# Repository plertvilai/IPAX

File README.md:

# In Situ Plankton Assemblage eXplorer

This Github repository contains all information necessary to build the In Situ Plankton Assemblage eXplorer (IPAX). Here is a brief introduction to how to utilize the repository. 

# Detailed Guide

A detail building guide is given in the Building Guide subfolder. Note that this guide is written in HTML format. To read it, simply download the entire folder and use a browser to open the file [index.html](https://github.com/plertvilai/IPAX/blob/master/Building%20Guide/index.html "index.html"). 

# Fabrication Files

There are two folders containing files that are necessary for IPAX fabrication.
1. **Mechanicals** contains STL files that can be directly sent to a 3D printer to printout the mechanical parts. A STEP file is also included for users that are interested to develop the system further. The STEP file [Assembly Rev02 Revised for BES v3.step](https://github.com/plertvilai/IPAX/blob/master/Mechanicals/Assembly%20Rev02%20Revised%20for%20BES%20v3.step "Assembly Rev02 Revised for BES v3.step") contains CAD files of all the parts, including waterproof housing from Bluerobotics that can be opened with a CAD software for further development.
2. **PCBs** contains all files for the printed circuit boards in the IPAX. Each subfolder is for each PCB, and the folder fabrication contains Gerber files that can be sent directly to PCB manufacturers. Each subfolder also contains KiCAD files that users can use to develop the PCBs for fit their needs. 

# Firmware
The folder Firmware contains all software for the IPAX. 
### Control Board
This subfolder contains Arduino (.ino) files that can be uploaded to the control board of the IPAX. 
1. full_control_alwaysON is the main routine for the control board that set the Raspberry Pi to always ON.
2. full_control_interval is the main routine for the control board that turns the Raspberry Pi ON only at the specified time.
3. rtc_set is a temporary code that can be uploaded to the control board to set the real-time clock.

### Raspberry Pi
This subfolder contains Python files for the Raspberry Pi on the IPAX. 
1. connectArduino.py is a routine that allows the Raspberry Pi to communicate with the Arduino on the control board.
2. ipaxClass.py is the library for the IPAX.
3. ipaxDeploy.py is the main routine for deploying the IPAX.
4. shutdowncheck.py is the control script that allows the Raspberry Pi to be properly shutdown with an external switch on the housing and the control board.

The configuration subfolder contains all the configuration files needed to configure that Raspberry Pi.

# Bill of Materials
The folder BOM contains a single MS Excel file (.xlsx) that contains the detailed bill of materials of the IPAX.

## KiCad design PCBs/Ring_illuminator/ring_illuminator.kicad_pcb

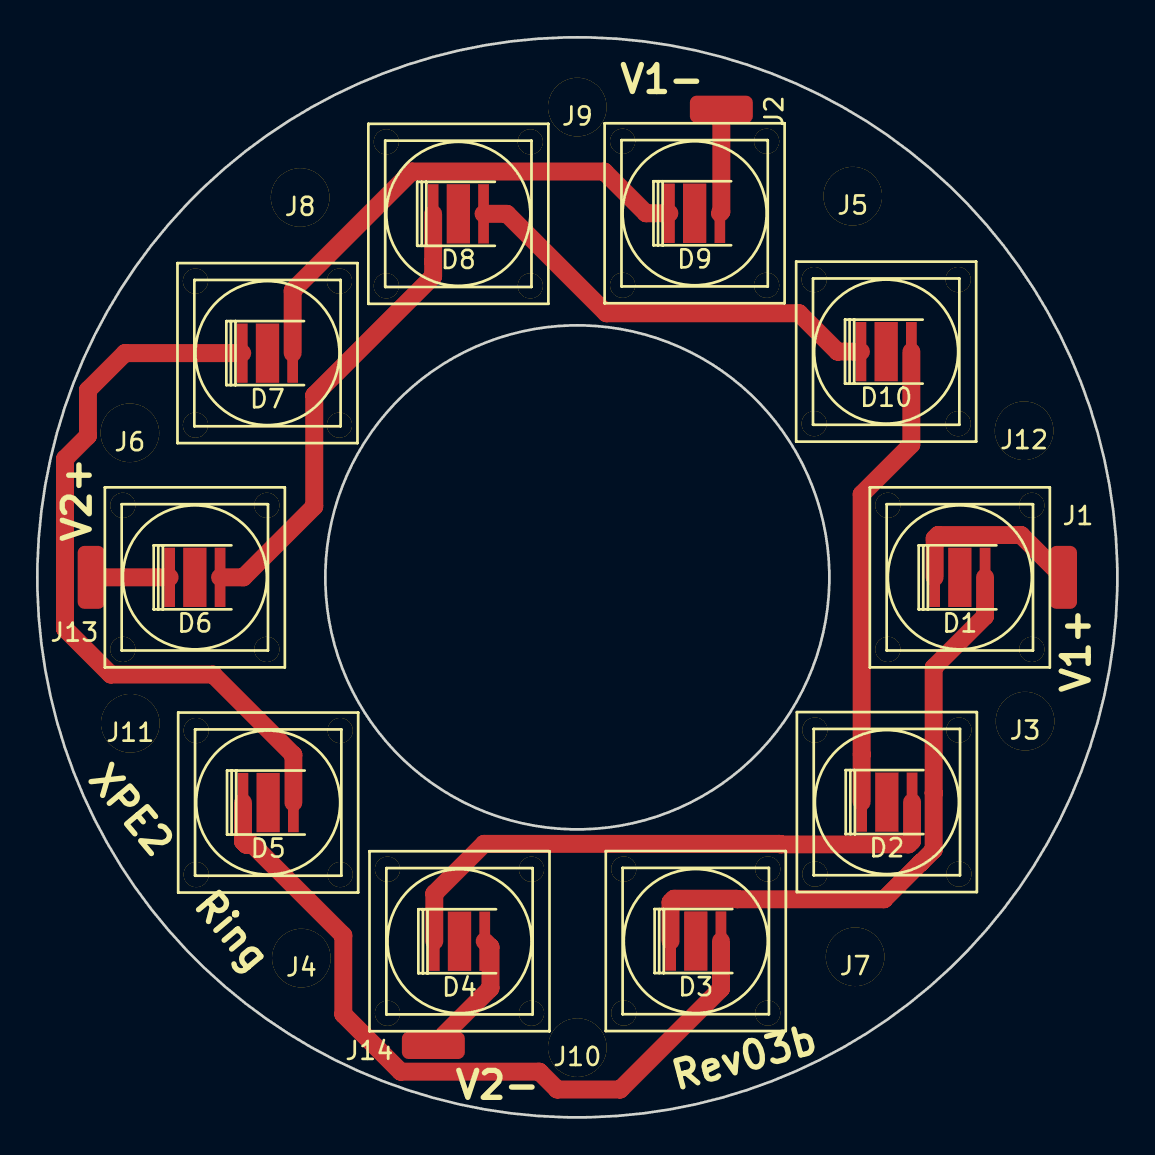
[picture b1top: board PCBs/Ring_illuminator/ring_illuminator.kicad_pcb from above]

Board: 2 copper layers, 60.0 x 60.0 mm, 24 parts (0 on the bottom side), 12 nets.

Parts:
D1, D2, D3, D4, D5, D6, D7, D8, D9, D10: LED; CREE_XTE_Carclo_10mm
J1, J2, J13, J14: Conn_01x01_Female; large_smd_pad
J3, J4, J5, J6, J7, J8, J9, J10, J11, J12: Conn_01x01_Female; SCREW_4

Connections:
LED1+: D1.2, J1.1
LED1-: D9.1, J2.1
LED2+: D6.2, J13.1
LED2-: D4.1, J14.1
unnamed: D1.1, D3.2
unnamed: D2.1, D4.2
unnamed: D3.1, D5.2
unnamed: D5.1, D7.2
unnamed: D6.1, D8.2
unnamed: D7.1, D9.2
unnamed: D2.2, D10.1
unnamed: D8.1, D10.2

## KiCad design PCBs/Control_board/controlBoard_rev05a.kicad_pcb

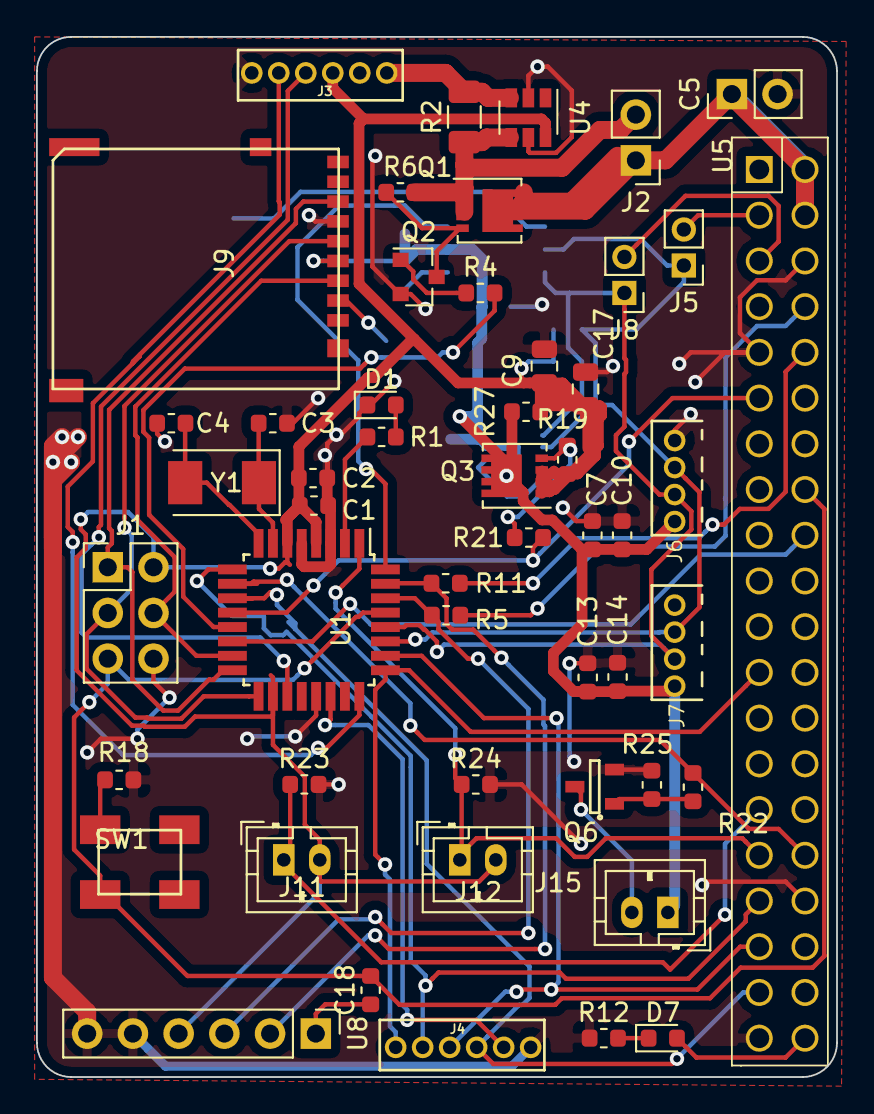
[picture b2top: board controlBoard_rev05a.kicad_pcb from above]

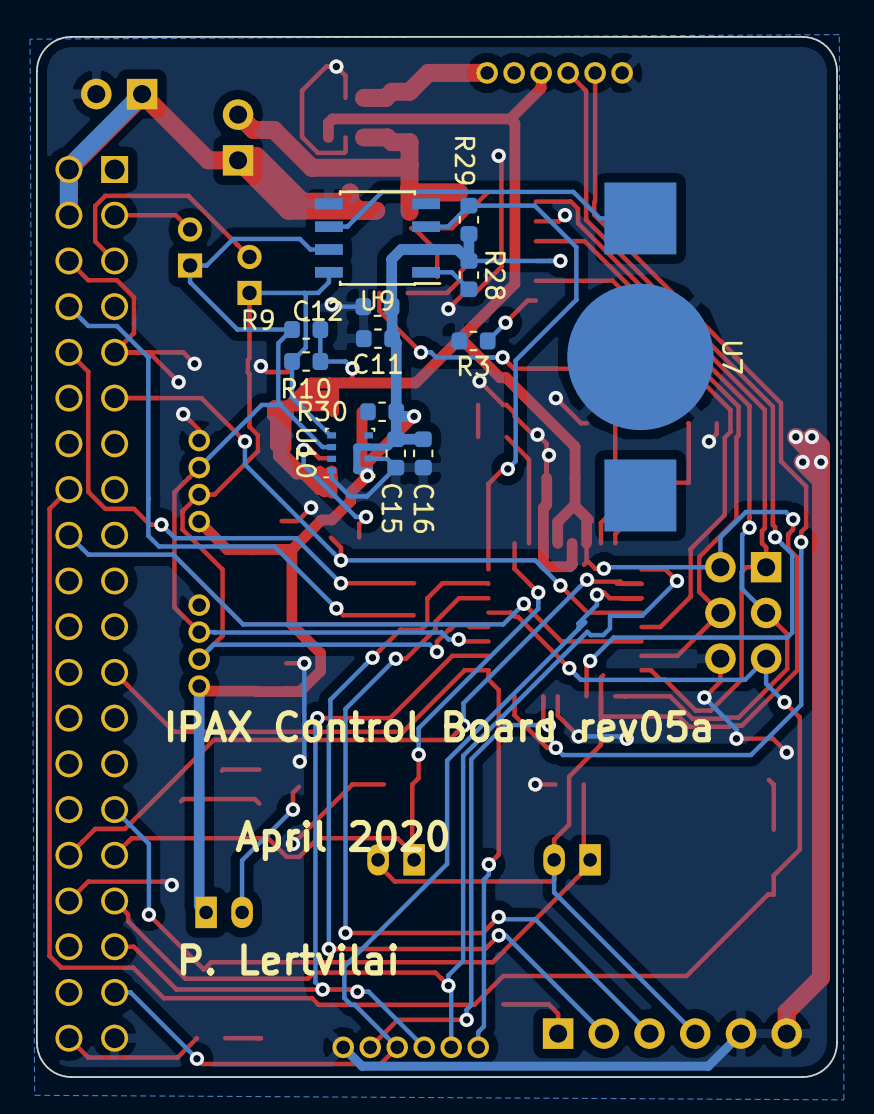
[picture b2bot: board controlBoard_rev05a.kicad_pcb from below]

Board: 2 copper layers, 44.5 x 57.8 mm, 64 parts (13 on the bottom side), 49 nets.

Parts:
C1, C10, C12, C14, C16: 1uF; C_0603_1608Metric
C2, C18: 0.1uF; C_0603_1608Metric
C3, C4: 22pF; C_0603_1608Metric
C5: CP; PinHeader_1x02_P2.54mm_Vertical
C7, C11, C13, C15: 10nF; C_0603_1608Metric
C9, C17: 22uF; C_0805_2012Metric
D1, D7: LED; LED_0603_1608Metric
J1: Conn_02x03_Odd_Even; PinHeader_2x03_P2.54mm_Vertical
J2: Conn_01x02_Male; PinHeader_1x02_P2.54mm_Vertical
J3, J4: Conn_01x06_Male; conn_1x06_1.5mm
J5, J8: Conn_01x02_Female; PinHeader_1x02_P2.00mm_Vertical
J6, J7: Conn_01x04_Male; conn_1x04_1.5mm
J9: Micro_SD_Card; DM3AT_microSD
J11, J12, J15: Conn_01x02_Male; JST_PH_B2B-PH-K_1x02_P2.00mm_Vertical
Q1, Q3: PMOS; Diodes_PowerDI3333-8
Q2: Q_NMOS_GSD; SOT-23
Q6: Q_NMOS_GSD; SOT-23-3
R1, R4, R5, R11, R12: 400R; R_0603_1608Metric
R2: 0.01R; R_1206_3216Metric
R3, R6, R9, R10, R18, R19, R23, R24, R25, R28, R29, R30: 10k; R_0603_1608Metric
R21, R22: 500R; R_0603_1608Metric
R27: jumper; R_0603_1608Metric
SW1: SW_DPST; SMD_pushbutton
U1: ATmega328P-AU; TQFP-32_7x7mm_P0.8mm
U4: INA181; SOT-23-6
U5: Pi_Header; RPi_Cobbler
U7: coin_cell; BK870_CR1025holder
U8: FTDI_Basic; PinHeader_1x06_P2.54mm_Vertical
U9: DS3231MZ; SOIC-8_3.9x4.9mm_P1.27mm
U10: BME280; Bosch_LGA-8_2.5x2.5mm_P0.65mm_ClockwisePinNumbering
Y1: Crystal; Crystal_SMD_Abracon_ABM3-2Pin_5.0x3.2mm

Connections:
3.3V_ARD: C1.1, C2.1, C9.1, C17.1, J1.2, J3.4, J11.2, J12.2, Q3.1, Q3.2, Q3.3, R9.1, R10.1, R19.2, R27.2, U1.4, U1.6, U1.18, U4.6, U8.4
3.3V_CTL: R21.1, U1.12, U5.6
3.3V_out: C7.1, C10.1, C11.1, C12.1, C13.1, C14.1, C15.1, C16.1, J6.1, J7.1, J9.4, J15.1, Q3.5, R27.1, R28.1, R29.1, R30.1, U9.2, U10.6, U10.8
5V: J2.2, Q1.1, Q1.2, Q1.3, R2.1, R6.2, U4.4
/Pi_SCL: J8.2, U5.3
/Pi_SDA: J5.2, U5.2
/powerControl/5V_IN: J3.6, R2.2, U4.3
CRYSTAL1: C3.1, U1.7, Y1.1
CRYSTAL2: C4.1, U1.8, Y1.2
CS: J9.2, R3.1
FAN_CTL: R22.2, U1.10, U5.25
Flash: J4.3, U1.11, U5.19
GND: C1.2, C2.2, C3.2, C4.2, C5.2, C7.2, C9.2, C10.2, C11.2, C12.2, C13.2, C14.2, C15.2, C16.2, C17.2, D1.1, J1.6, J3.1, J4.1, J6.4, J7.4, J9.6, Q2.2, Q6.2, R3.2, R12.1, R18.2, R23.2, R24.2, R25.1, U1.3, U1.5, U1.21, U4.2, U4.5, U5.5, U5.20, U5.24, U5.38, U7.1, U8.5, U8.6, U9.5, U10.1, U10.7
I_BATT: J3.3, U1.19
I_LED: J4.2, U1.22
LED_EN: J4.5, U1.9, U5.17
LED_EN2: J4.6, U1.25, U5.12
MISO: J1.1, J9.7, U1.16
MOSI: J1.4, J9.3, U1.15
unnamed: C18.1, U8.1
unnamed: D1.2, R1.1
unnamed: D7.1, R12.2
unnamed: D7.2, U5.21
unnamed: J15.2, Q6.3
unnamed: Q1.4, Q2.3, R6.1
unnamed: Q2.1, R4.1
unnamed: Q3.4, R19.1, R21.2
unnamed: Q6.1, R22.1, R25.2
unnamed: R1.2, U1.2
unnamed: R5.2, U5.37
unnamed: R11.2, U5.36
unnamed: R18.1, SW1.3
unnamed: R28.2, U9.1
unnamed: R30.2, U10.5
unnamed: U7.3, U9.6
PI_CTL: R4.2, U1.13
PI_SIG: U1.14, U5.32
PUSH: J11.1, R23.1, U5.15
PUSH2: J12.1, R24.1, U1.1, U5.16
RST: C18.2, J1.5, SW1.4, U1.29, U5.33
RXD: R5.1, U1.30, U8.3
SCK: J1.3, J9.5, U1.17
SCL: J6.2, J7.2, J8.1, R10.2, U1.28, U9.8, U10.4
SDA: J5.1, J6.3, J7.3, R9.2, U1.27, U9.7, U10.3
TXD: R11.1, U1.31, U8.2
Torch: J4.4, U1.26, U5.18
V_BATT: J3.2, U1.24
Vpi: C5.1, J2.1, Q1.5, U5.39, U5.40
alarm: R29.2, U1.32, U9.3

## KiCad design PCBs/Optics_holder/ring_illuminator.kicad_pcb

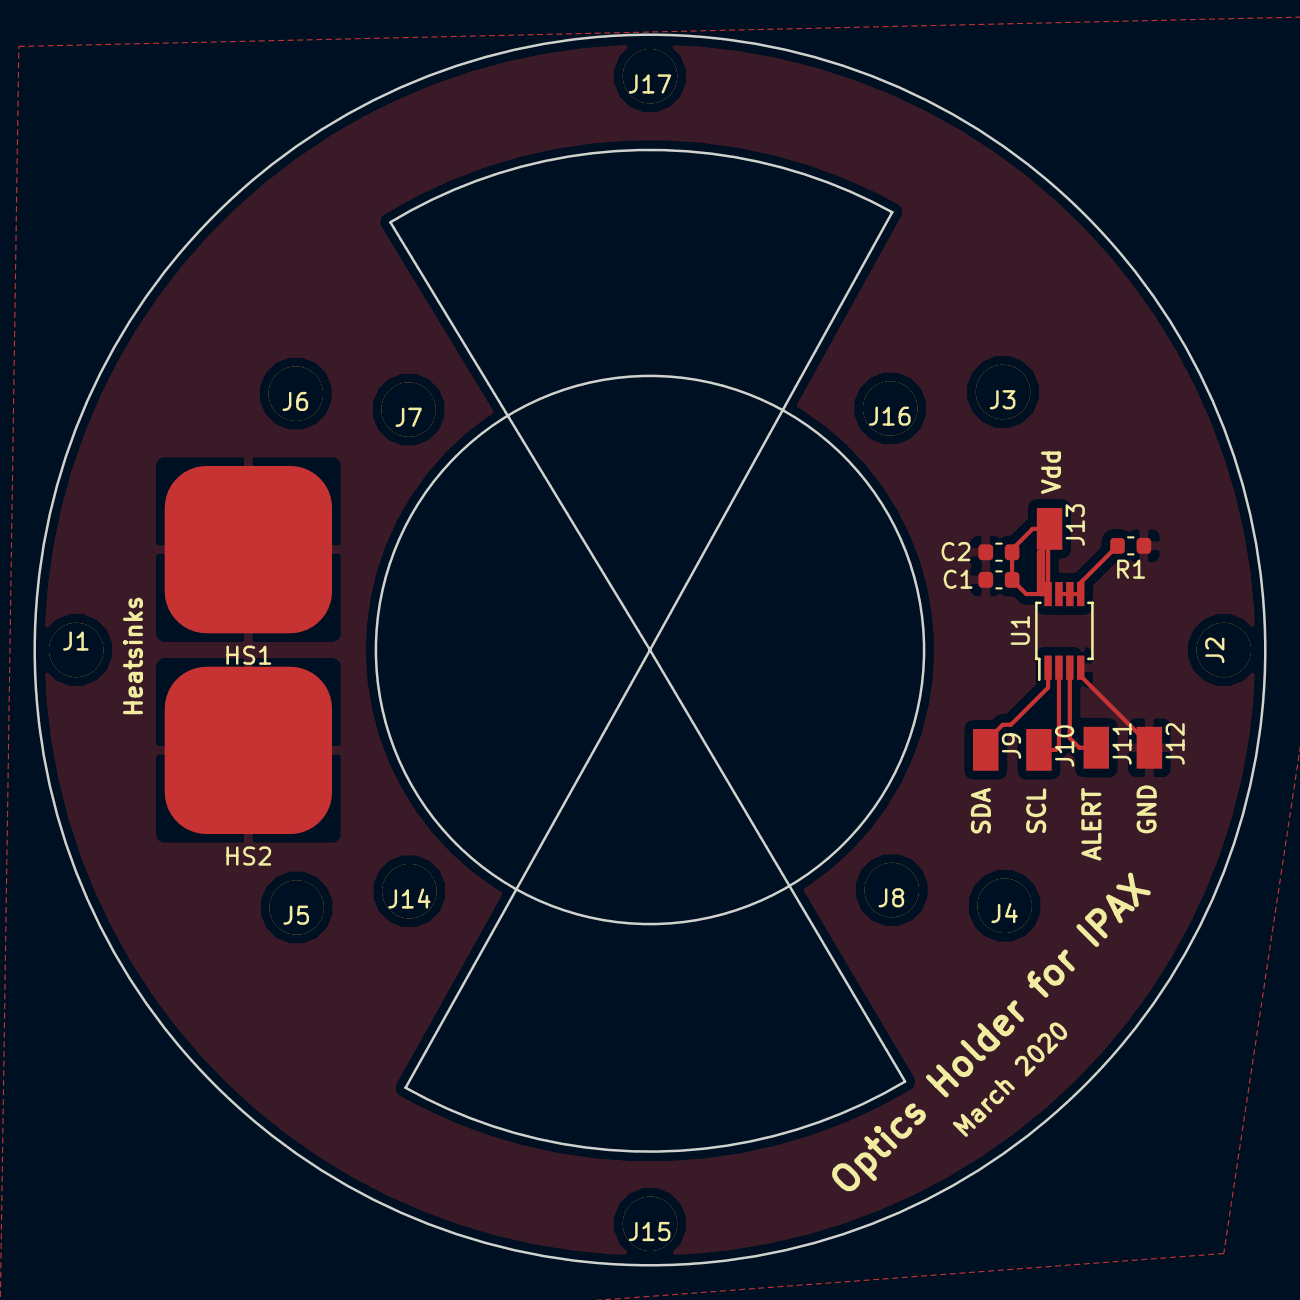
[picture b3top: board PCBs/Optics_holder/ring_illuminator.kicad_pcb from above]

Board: 2 copper layers, 73.5 x 73.5 mm, 23 parts (0 on the bottom side), 6 nets.

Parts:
C1, C2: C; C_0603_1608Metric
HS1, HS2: Heatsink_Pad; HeatSink_10x10mm
J1, J2, J3, J4, J5, J6, J7, J8, J14, J15, J16, J17: Conn_01x01_Female; SCREW_4
J9, J10, J11, J12, J13: Conn_01x01_Male; small_smd_pad
R1: 10k; R_0603_1608Metric
U1: MCP9808; MSOP-8_3x3mm_P0.65mm

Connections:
/A0: R1.2, U1.5, U1.6, U1.7
/ALERT: J11.1, U1.3
/SCL: J10.1, U1.2
/SDA: J9.1, U1.1
/Vdd: C1.1, C2.1, J13.1, U1.8
GND: C1.2, C2.2, HS1.1, HS2.1, J12.1, R1.1, U1.4

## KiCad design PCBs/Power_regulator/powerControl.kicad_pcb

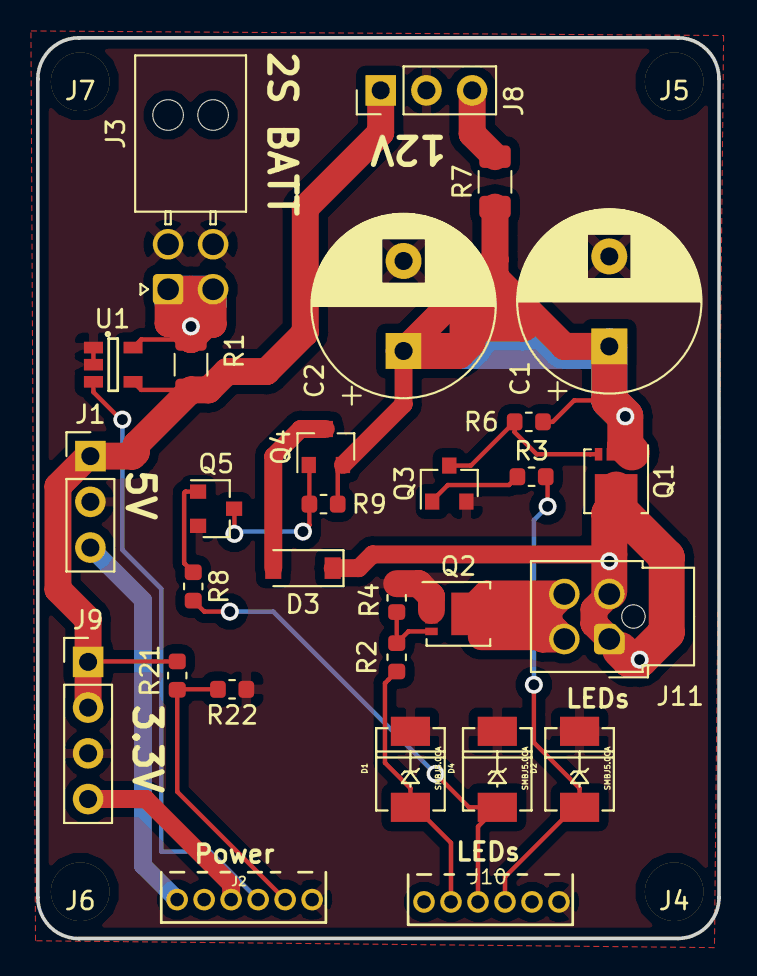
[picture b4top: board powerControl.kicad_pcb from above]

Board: 2 copper layers, 37.8 x 50.0 mm, 33 parts (0 on the bottom side), 20 nets.

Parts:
C1, C2: 470uF; CP_Radial_D10.0mm_P5.00mm
D1, D2, D4: SMBJ5.0CA; DO-214AA
D3: NSI450-20AT1G; D_SOD-123
J1, J8: Conn_01x03_Female; PinHeader_1x03_P2.54mm_Vertical
J2: Conn_01x06_Female; conn_1x06_1.5mm
J3: Conn_01x04_Male; Molex_Nano-Fit_105314-xx04_2x02_P2.50mm_Horizontal
J4, J5, J6, J7: Conn_01x01_Male; SCREW_4
J9: Conn_01x04_Female; PinHeader_1x04_P2.54mm_Vertical
J10: Conn_01x06_Male; conn_1x06_1.5mm
J11: Conn_01x04_Male; Molex_Nano-Fit_105310-xx04_2x02_P2.50mm_Vertical
Q1: PMOS; Diodes_PowerDI3333-8
Q2: NMOS; Diodes_PowerDI3333-8
Q3, Q5: Q_NMOS_GSD; SOT-23
Q4: Q_PMOS_GSD; SOT-23
R1: 0.01R; R_1206_3216Metric
R2, R3, R8: 400R; R_0603_1608Metric
R4, R6, R9, R21: 10k; R_0603_1608Metric
R7: 10R; R_1206_3216Metric
R22: 20k; R_0603_1608Metric
U1: MAX9938; SOT-23-5

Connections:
/3.3V: J2.4, J9.4
/5V: J1.3, J2.6
/12V: J8.3, R7.2
/I_batt: J2.3, U1.3
/Vbatt_in: J3.1, J3.2, R1.2, U1.5
/Vbatt_out: J1.1, J8.1, J9.1, J9.2, R1.1, R21.2, U1.4
/batt_sense: J2.2, R21.1, R22.2
Flash: D2.1, J10.3, R3.2
GND: C1.2, C2.2, D1.2, D2.2, D4.2, J1.2, J2.1, J3.3, J3.4, J8.2, J9.3, J10.1, Q2.1, Q2.2, Q2.3, Q3.2, Q5.2, R4.1, R22.1, U1.1, U1.2
LED+: D3.1, J11.1, J11.2, Q1.5
LED-: J11.3, J11.4, Q2.5
LED_EN: D1.1, J10.5, R2.2
unnamed: D3.2, Q4.3
unnamed: Q1.4, Q3.3, R6.1
unnamed: Q2.4, R2.1, R4.2
unnamed: Q3.1, R3.1
unnamed: Q4.1, Q5.3, R9.1
unnamed: Q5.1, R8.1
Torch: D4.1, J10.4, R8.2
V_LED: C1.1, C2.1, Q1.1, Q1.2, Q1.3, Q4.2, R6.2, R7.1, R9.2

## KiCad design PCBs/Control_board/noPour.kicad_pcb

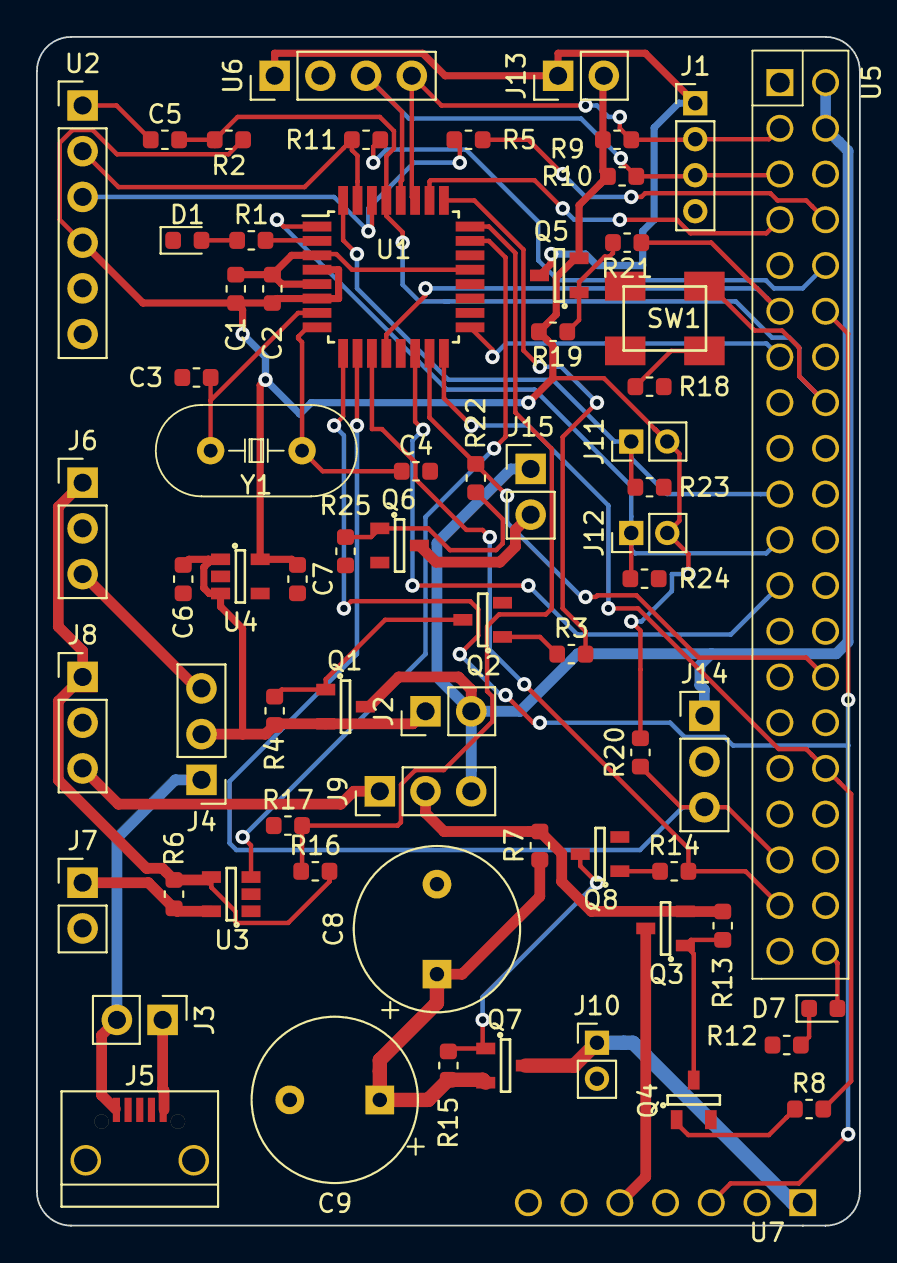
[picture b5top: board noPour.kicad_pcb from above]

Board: 2 copper layers, 45.7 x 66.0 mm, 68 parts (0 on the bottom side), 52 nets.

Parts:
C1, C6, C7: 1uF; C_0603_1608Metric
C2, C5: 0.1uF; C_0603_1608Metric
C3, C4: 22pF; C_0603_1608Metric
C8, C9: 1000uF; CP_Radial_Tantal_D9.0mm_P5.00mm
D1, D7: LED; LED_0603_1608Metric
J1: Conn_01x04_Male; PinHeader_1x04_P2.00mm_Vertical
J2, J3, J7, J13, J15: Conn_01x02_Male; PinHeader_1x02_P2.54mm_Vertical
J4, J6, J8, J9, J14: Conn_01x03_Male; PinHeader_1x03_P2.54mm_Vertical
J5: USB_B_Micro; USB_Micro-B_eBay
J10, J11, J12: Conn_01x02_Male; PinHeader_1x02_P2.00mm_Vertical
Q1, Q3, Q5, Q7: Q_PMOS_GSD; SOT-23-3
Q2, Q4, Q6, Q8: Q_NMOS_GSD; SOT-23-3
R1, R3, R5, R8, R11, R12, R14: 400R; R_0603_1608Metric
R2, R4, R9, R10, R13, R15, R18, R23, R24: 10k; R_0603_1608Metric
R6: 0.01R; R_0603_1608Metric
R7, R16, R17, R19, R20, R21, R22, R25: R; R_0603_1608Metric
SW1: SW_DPST; SMD_pushbutton
U1: ATmega328P-AU; TQFP-32_7x7mm_P0.8mm
U2: FTDI_Basic; PinHeader_1x06_P2.54mm_Vertical
U3: MAX9938; SOT-23-5
U4: AP2112; SOT-23-5
U5: Pi_Header; RPi_Cobbler
U6: OLED_I2C; PinHeader_1x04_P2.54mm_Vertical
U7: LUXdriver; LUXdrive
Y1: Crystal; CRYSTAL_TH

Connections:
3.3V: C1.1, C2.1, C7.1, J11.2, J12.2, J13.2, Q5.2, R2.1, R9.1, R10.1, R19.2, R20.2, U1.4, U1.6, U2.4, U4.5
3.3V_CTL: R21.1, U1.12, U5.6
3.3V_out: J1.1, J13.1, Q5.3, U6.1
12V: J8.3, J9.1
Batt_sense: R16.1, R17.2, U1.24
CRYSTAL1: C3.1, U1.7, Y1.1
CRYSTAL2: C4.1, U1.8, Y1.2
CUR_OUT: U1.23, U3.3
FAN_CTL: R22.2, U1.15, U5.27
Flash: R14.2, U1.11, U5.19
GND: C1.2, C2.2, C3.2, C4.2, C6.2, C7.2, C8.2, C9.2, D1.1, J1.4, J3.1, J5.5, J6.2, J7.2, J8.2, J10.2, J14.2, Q2.2, Q4.2, Q6.2, Q8.2, R12.1, R17.1, R18.2, R23.2, R24.2, R25.1, U1.3, U1.5, U1.21, U2.5, U2.6, U3.1, U3.2, U4.2, U5.5, U5.20, U5.24, U5.38, U6.2, U7.2, U7.7
GPIO4: U1.26, U5.4
GPIO10: U1.14, U5.12
GPIO27: U1.17, U5.7
LED+: J10.1, Q7.3, U7.1
LED_CTL: R8.2, U1.16, U5.25
LEDdim: U1.9, U5.35, U7.3
LUXin: Q3.3, U7.5
unnamed: C5.1, U2.1
unnamed: D1.2, R1.1
unnamed: D7.1, R12.2
unnamed: D7.2, U5.21
unnamed: J15.2, Q6.3
unnamed: Q1.1, Q2.3, R4.1
unnamed: Q2.1, R3.1
unnamed: Q3.1, Q4.3, R13.1
unnamed: Q4.1, R8.1
unnamed: Q5.1, R19.1, R21.2
unnamed: Q6.1, R22.1, R25.2
unnamed: Q7.1, Q8.3, R15.1
unnamed: Q8.1, R14.1
unnamed: R1.2, U1.2
unnamed: R5.2, U5.37
unnamed: R11.2, U5.36
unnamed: R18.1, SW1.3
PI_CTL: R3.2, U1.25
PUSH: J11.1, R23.1, U1.32, U5.10
PUSH2: J12.1, R24.1, U1.1, U5.11
RST: C5.2, R2.2, SW1.4, U1.29, U5.33
RXD: R5.1, U1.30, U2.3
SCL: J1.3, R10.2, U1.28, U5.3, U6.3
SDA: J1.2, R9.2, U1.27, U5.2, U6.4
TXD: R11.1, U1.31, U2.2
V_FLASH: C8.1, C9.1, Q7.2, R7.1, R15.2
V_LED: J9.2, Q3.2, R7.2, R13.2
Vbatt: J6.1, J8.1, R6.1, R16.2, U3.4
Vbatt0: J7.1, R6.2, U3.5
Vbatt_out: J4.3, J6.3
Vhall: J14.3, R20.1, U1.10, U5.18
Vin: C6.1, J2.1, J4.2, Q1.2, R4.2, U4.1, U4.3
Vpi: J2.2, J9.3, J14.1, J15.1, Q1.3, U5.39, U5.40
Vusb: J3.2, J4.1, J5.1

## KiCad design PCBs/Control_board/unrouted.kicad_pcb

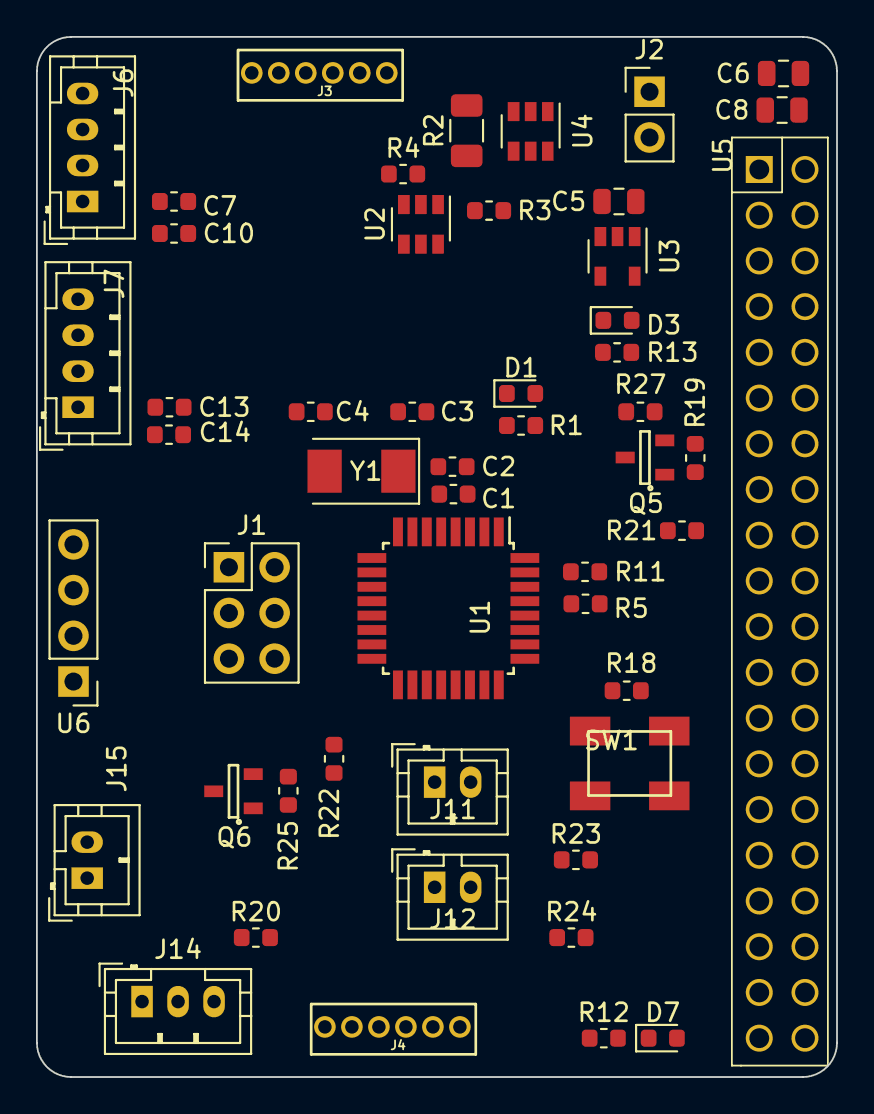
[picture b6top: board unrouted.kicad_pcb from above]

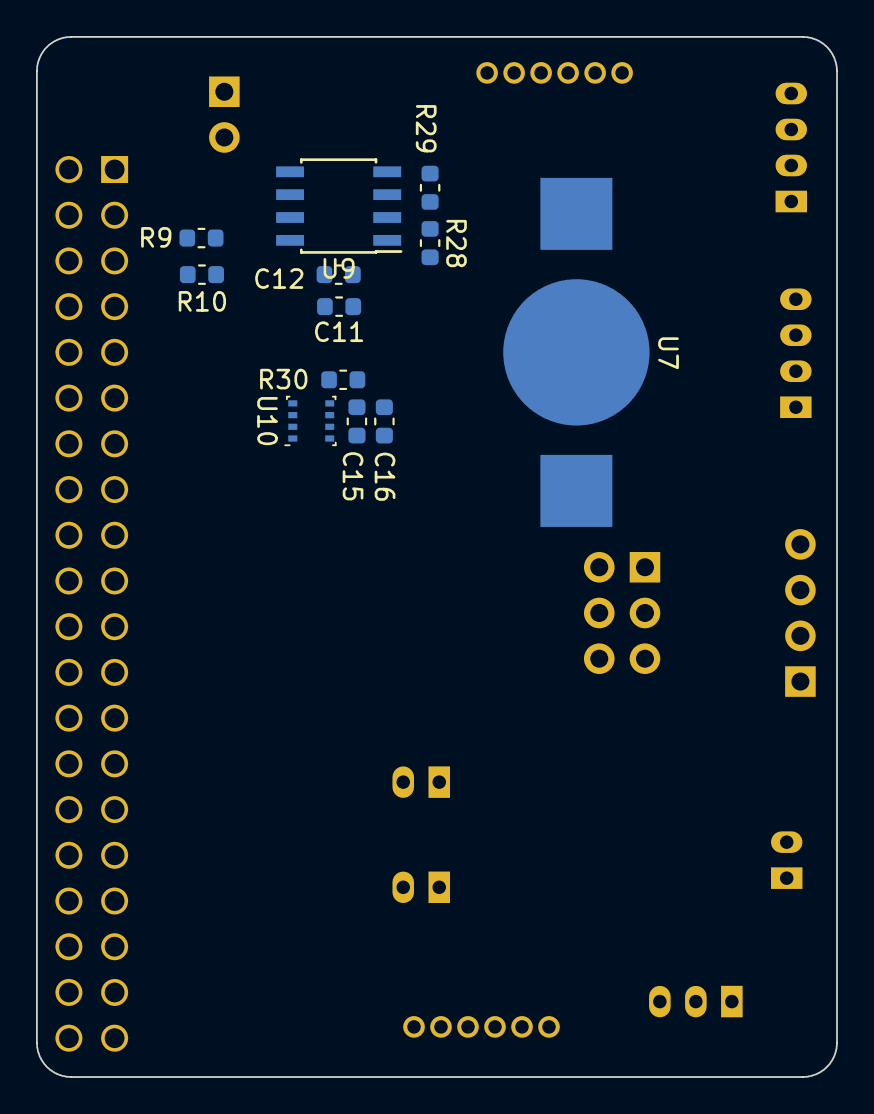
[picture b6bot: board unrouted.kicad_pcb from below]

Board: 2 copper layers, 44.5 x 57.8 mm, 63 parts (12 on the bottom side), 51 nets, no tracks yet.

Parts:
C1, C10, C12, C14, C16: 1uF; C_0603_1608Metric
C2: 0.1uF; C_0603_1608Metric
C3, C4: 22pF; C_0603_1608Metric
C5, C6, C8: 10uF; C_0805_2012Metric
C7, C11, C13, C15: 10nF; C_0603_1608Metric
D1, D7: LED; LED_0603_1608Metric
D3: RED; LED_0603_1608Metric
J1: Conn_02x03_Odd_Even; PinHeader_2x03_P2.54mm_Vertical
J2: Conn_01x02_Male; PinHeader_1x02_P2.54mm_Vertical
J3, J4: Conn_01x06_Male; conn_1x06_1.5mm
J6, J7: Conn_01x04_Male; JST_PH_B4B-PH-K_1x04_P2.00mm_Vertical
J11, J12, J15: Conn_01x02_Male; JST_PH_B2B-PH-K_1x02_P2.00mm_Vertical
J14: Conn_01x03_Male; JST_PH_B3B-PH-K_1x03_P2.00mm_Vertical
Q5: Q_PMOS_GSD; SOT-23-3
Q6: Q_NMOS_GSD; SOT-23-3
R1, R3, R5, R11, R12: 400R; R_0603_1608Metric
R2: 0.01R; R_1206_3216Metric
R4, R9, R10, R13, R18, R19, R20, R23, R24, R25, R28, R29, R30: 10k; R_0603_1608Metric
R21, R22: 500R; R_0603_1608Metric
R27: jumper; R_0603_1608Metric
SW1: SW_DPST; SMD_pushbutton
U1: ATmega328P-AU; TQFP-32_7x7mm_P0.8mm
U2: CEH2609_NP_Mosfet; SOT-23-6
U3: NCP361; SOT-23-5
U4: INA181; SOT-23-6
U5: Pi_Header; RPi_Cobbler
U6: OLED_I2C; PinHeader_1x04_P2.54mm_Vertical
U7: coin_cell; BK870_CR1025holder
U9: DS3231MZ; SOIC-8_3.9x4.9mm_P1.27mm
U10: BME280; Bosch_LGA-8_2.5x2.5mm_P0.65mm_ClockwisePinNumbering
Y1: Crystal; Crystal_SMD_Abracon_ABM3-2Pin_5.0x3.2mm

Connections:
3.3V: J11.2, J12.2, Q5.2, R9.1, R10.1, R19.2, R27.2, U5.1
3.3V_ARD: C1.1, C2.1, J1.2, J3.4, R20.2, U1.4, U1.6, U4.6
3.3V_CTL: R21.1, U1.12, U5.6
3.3V_out: C7.1, C10.1, C11.1, C12.1, C13.1, C14.1, C15.1, C16.1, J6.1, J7.1, Q5.3, R27.1, R28.1, R29.1, R30.1, U6.1, U9.2, U10.6, U10.8
5V: J2.2, J14.1, R2.1, R4.2, U2.2, U4.4
5V_EN: J3.5, U1.14
/powerControl/5V_IN: J3.6, R2.2, U4.3
/powerControl/5V_NPTC: C5.1, U2.4, U3.1
CRYSTAL1: C3.1, U1.7, Y1.1
CRYSTAL2: C4.1, U1.8, Y1.2
FAN_CTL: R22.2, U1.10, U5.27
Flash: J4.3, U1.11, U5.19
GND: C1.2, C2.2, C3.2, C4.2, C5.2, C6.2, C7.2, C8.2, C10.2, C11.2, C12.2, C13.2, C14.2, C15.2, C16.2, D1.1, J1.6, J3.1, J4.1, J6.4, J7.4, J14.2, Q6.2, R12.1, R18.2, R23.2, R24.2, R25.1, U1.3, U1.5, U1.21, U2.5, U3.2, U3.3, U4.2, U4.5, U5.5, U5.20, U5.24, U5.38, U6.2, U7.1, U9.5, U10.1, U10.7
I_BATT: J3.3, U1.23
I_LED: J4.2, U1.25
I_PI: U1.22, U4.1
LED_EN: J4.5, U1.9, U5.35
LED_SENSE: J4.6, U1.19
MISO: J1.1, U1.16
MOSI: J1.4, U1.15
unnamed: D1.2, R1.1
unnamed: D3.1, U3.4
unnamed: D3.2, R13.2
unnamed: D7.1, R12.2
unnamed: D7.2, U5.21
unnamed: J15.2, Q6.3
unnamed: Q5.1, R19.1, R21.2
unnamed: Q6.1, R22.1, R25.2
unnamed: R1.2, U1.2
unnamed: R3.1, U2.1
unnamed: R4.1, U2.3, U2.6
unnamed: R5.2, U5.37
unnamed: R11.2, U5.36
unnamed: R18.1, SW1.3
unnamed: R28.2, U9.1
unnamed: R30.2, U10.5
unnamed: U7.2, U7.3, U9.6
PI_CTL: R3.2, U1.13
PUSH: J11.1, R23.1, U5.10
PUSH2: J12.1, R24.1, U5.11
RST: J1.5, SW1.4, U1.29, U5.33
RXD: R5.1, U1.30
SCK: J1.3, U1.17
SCL: J6.2, J7.2, R10.2, U1.28, U5.3, U6.3, U9.8, U10.4
SDA: J6.3, J7.3, R9.2, U1.27, U5.2, U6.4, U9.7, U10.3
TXD: R11.1, U1.31
Torch: J4.4, U1.26
V_BATT: J3.2, U1.24
Vhall: J14.3, R20.1, U1.1, U5.18
Vpi: C6.1, C8.1, J2.1, J15.1, U3.5, U5.39, U5.40
alarm: R29.2, U1.32, U9.3

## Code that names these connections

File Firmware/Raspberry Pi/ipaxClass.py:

#!/usr/bin/python

# Library for IPAX
# P. Lertvilai
# Updated for Control Board Rev04 
# March 17, 2020

import io
import os
import time
#import cv2
import picamera
import numpy as np
import RPi.GPIO as GPIO
import datetime as dt

#------------------------pin assignment------------------------------#
#for IPAX, on-board led on pin 21 is controlled by connectArduino.py instead

button_pin = 10 #for push button
fan_pin = 27 #for fan control; not used in PUE v4.0
peri_pin = 17 #3.3V peripheral control; not useby Pi; Arduino controls all power management.
led_en_pin = 18 #low side control of LED
torch_pin = 19 # torch mode control for LED
# LED flash mode is pin 26; controlled directly through camera hardware
#hall_pin = 11 #for interrupt by Hall sensor; unused on Pi


class IPAX():

	def __init__(self):
		#GPIO
		self.buttonState = 0 #read button state at the beginning
		self.ledState = 0 #led pin state

		#file IO
		self.imageN = 30
		self.framerate = 50

		#get the next available still image number
		i = 0
		while os.path.exists("/home/pi/PUV/image/img%.5d_0.jpg" % i):
			i += 1
		self.imNum = i #use for still images

		#get the next available video number
		i = 0
		while os.path.exists("/home/pi/PUV/image/video%.5d.h264" % i):
			i += 1
		self.vidNum = i

		#camera
		self.camera = 0

		#time keeping
		self.time = time.time()
		self.recStart = 0
		self.recEnd = 0

		#others
		self.mode = 0

	def initialize(self):
		'''Initialize the GPIO pins of the instrument.
		Needs to be run at first for GPIO to function properly.
		Then, read the configuration file and set varaibles accordingly.'''
		GPIO.setmode(GPIO.BCM)
		GPIO.setup(button_pin, GPIO.IN)
		GPIO.setup(fan_pin, GPIO.OUT)
		GPIO.output(fan_pin, GPIO.LOW)
		GPIO.setup(led_en_pin, GPIO.OUT)
		GPIO.output(led_en_pin, GPIO.LOW)
		GPIO.setup(peri_pin, GPIO.OUT)
		GPIO.output(peri_pin, GPIO.HIGH) #3.3V CTL is active LOW 
		GPIO.setup(torch_pin, GPIO.OUT)

		self.buttonState = GPIO.input(button_pin)
		self.ledState = 0
		
		return True

	def ledON(self):
		'''Turn LED on.'''
		self.ledState = 1
		GPIO.output(led_en_pin, GPIO.HIGH)
		return True

	def ledOFF(self):
		'''Turn LED off.'''
		self.ledState = 0
		GPIO.output(led_en_pin, GPIO.LOW)
		return True

	def torchON(self):
		'''turn LED on torch mode.'''
		GPIO.output(torch_pin, GPIO.HIGH)
		return True

	def torchOFF(self):
		'''turn LED on torch mode.'''
		GPIO.output(torch_pin, GPIO.LOW)
		return True

	def cameraInit(self,shutter_speed=2500,resolution = (3280,2464),iso=200,awb_gains=(1.1,2.5)):
		'''Initialize camera.'''
		self.camera = picamera.PiCamera()
		self.camera.shutter_speed = shutter_speed #in microseconds
		self.camera.iso = iso
		self.camera.awb_mode = 'off'
		self.camera.awb_gains = awb_gains
		self.camera.resolution = resolution
		self.camera.flash_mode = 'on'
		self.camera.framerate = 30
		time.sleep(2) #wait for gain adjustment
		self.camera.exposure_mode = 'off'
		return True


	def cameraRelease(self):
		'''Release camera resources.'''
		print 'Closing camera'
		self.camera.close()
		#time.sleep(5)
		return True

	def oneShot(self,directory):
		'''Take one long exposure shot'''
		#self.ledON() #turn LED ON
		self.torchOFF() #make sure that torch mode is OFF
		#self.camera.capture(directory+'img%.5d_0.jpg'%(self.imNum))
		self.camera.capture(directory+'%d.jpg'%(time.time()))
		#self.ledOFF() #turn led off
		return True

	def videoRec(self,directory,recT):
		'''Take one long exposure shot'''
		#self.ledON() #turn LED ON
		self.torchOFF() #make sure that torch mode is OFF
		#self.camera.capture(directory+'img%.5d_0.jpg'%(self.imNum))
		self.camera.start_recording(directory+'%d.h264'%(time.time()))
		self.camera.wait_recording(recT)
		self.camera.stop_recording()
		#self.ledOFF() #turn led off
		return True

	def doubleShot(self,directory):
		'''Take two consecutive images. For use with PIV'''
		#self.ledON() #turn LED ON
		self.torchOFF() #make sure that torch mode is OFF
		self.camera.capture_sequence([directory+'img%.5d_0.jpg'%(self.imNum),directory+'img%.5d_1.jpg'%(self.imNum)])
		#self.ledOFF() #turn led off
		return True

	def recordInfo(self,directory,pressure,temp):
		'''Record image info to files.
		Mode == 0 -> video mode; else burst shot mode.'''
		file = open(directory+'stillAux.csv','a') 
		file.write('%.1f,%d,%.2f,%.2f\n'%(time.time(),self.imNum,pressure,temp))
		return True

	def incrementImNum(self):
		self.imNum = self.imNum+1

	def checkButtonStat(self):
		'''Check whether the button is released.
		3 is the default state where button is not pressed.
		1 is when button is kept pressed.
		4 button release
		2 button initial press'''
		buttonPress = GPIO.input(button_pin) #read button
		if buttonPress and self.buttonState: #if the button is pressed (from being pressed)
			self.buttonState = 1 #change button state
			return 1
		elif buttonPress and not self.buttonState: #if the button is pressed (from not being pressed)
			self.buttonState = 1
			return 2
		elif not buttonPress and not self.buttonState: #if the button is not pressed (from not being pressed)
			self.buttonState = 0
			return 3
		elif not buttonPress and self.buttonState: #if the button is not pressed (from being pressed)
			self.buttonState = 0
			return 4
		else:
			return 5

	def readButton(self):
		return GPIO.input(button_pin)

	def buttonCommand(self,timeOut=3):
		'''Accept command from one button.
		The timeout is in second and default to 3s.'''
		start = time.time()
		count = 0
		while(time.time()-start<timeOut):
			if self.checkButtonStat() == 2: #if button is pressed from not pressed
				count = count+1
				time.sleep(0.3) #for debouncing
			time.sleep(0.1) 
		return count

	def checkTime(self,second):
		'''check whether time has passed in second.'''
		if time.time()-self.time>second:
			self.time = time.time()
			return True
		else:
			return False

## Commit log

2020-03-30 Update for BES publication
2020-04-15 First upload building guide
2020-04-15 Bump brace-expansion in /Building Guide/assets/plugins/stickyfill
    Bumps [brace-expansion](https://github.com/juliangruber/brace-expansion) from 1.1.6 to 1.1.11.
    - [Release notes](https://github.com/juliangruber/brace-expansion/releases)
    - [Commits](https://github.com/juliangruber/brace-expansion/compare/v1.1.6...1.1.11)
2020-04-15 Update for revision05a
2020-05-01 Bump acorn in /Building Guide/assets/plugins/lightbox
    Bumps [acorn](https://github.com/acornjs/acorn) from 5.5.3 to 5.7.4.
    - [Release notes](https://github.com/acornjs/acorn/releases)
    - [Commits](https://github.com/acornjs/acorn/compare/5.5.3...5.7.4)
2020-06-03 Add descriptions for repository
2020-06-08 Bump websocket-extensions in /Building Guide/assets/plugins/stickyfill
    Bumps [websocket-extensions](https://github.com/faye/websocket-extensions-node) from 0.1.1 to 0.1.4.
    - [Release notes](https://github.com/faye/websocket-extensions-node/releases)
    - [Changelog](https://github.com/faye/websocket-extensions-node/blob/master/CHANGELOG.md)
    - [Commits](https://github.com/faye/websocket-extensions-node/compare/0.1.1...0.1.4)
2020-07-20 Bump lodash in /Building Guide/assets/plugins/lightbox
    Bumps [lodash](https://github.com/lodash/lodash) from 4.17.4 to 4.17.19.
    - [Release notes](https://github.com/lodash/lodash/releases)
    - [Commits](https://github.com/lodash/lodash/compare/4.17.4...4.17.19)
2020-08-01 Bump elliptic in /Building Guide/assets/plugins/lightbox
    Bumps [elliptic](https://github.com/indutny/elliptic) from 6.4.0 to 6.5.3.
    - [Release notes](https://github.com/indutny/elliptic/releases)
    - [Commits](https://github.com/indutny/elliptic/compare/v6.4.0...v6.5.3)
2020-12-12 Bump ini from 1.3.5 to 1.3.8 in /Building Guide/assets/plugins/lightbox
    Bumps [ini](https://github.com/isaacs/ini) from 1.3.5 to 1.3.8.
    - [Release notes](https://github.com/isaacs/ini/releases)
    - [Commits](https://github.com/isaacs/ini/compare/v1.3.5...v1.3.8)
2021-03-10 Bump elliptic in /Building Guide/assets/plugins/lightbox
    Bumps [elliptic](https://github.com/indutny/elliptic) from 6.4.0 to 6.5.4.
    - [Release notes](https://github.com/indutny/elliptic/releases)
    - [Commits](https://github.com/indutny/elliptic/compare/v6.4.0...v6.5.4)
2021-03-31 Bump y18n from 3.2.1 to 3.2.2 in /Building Guide/assets/plugins/lightbox
    Bumps [y18n](https://github.com/yargs/y18n) from 3.2.1 to 3.2.2.
    - [Release notes](https://github.com/yargs/y18n/releases)
    - [Changelog](https://github.com/yargs/y18n/blob/master/CHANGELOG.md)
    - [Commits](https://github.com/yargs/y18n/commits)
2021-05-07 Bump grunt in /Building Guide/assets/plugins/stickyfill
    Bumps [grunt](https://github.com/gruntjs/grunt) from 1.0.2 to 1.3.0.
    - [Release notes](https://github.com/gruntjs/grunt/releases)
    - [Changelog](https://github.com/gruntjs/grunt/blob/main/CHANGELOG)
    - [Commits](https://github.com/gruntjs/grunt/compare/v1.0.2...v1.3.0)
2021-05-11 Bump lodash in /Building Guide/assets/plugins/lightbox
    Bumps [lodash](https://github.com/lodash/lodash) from 4.17.4 to 4.17.21.
    - [Release notes](https://github.com/lodash/lodash/releases)
    - [Commits](https://github.com/lodash/lodash/compare/4.17.4...4.17.21)
2021-05-11 Bump hosted-git-info in /Building Guide/assets/plugins/stickyfill
    Bumps [hosted-git-info](https://github.com/npm/hosted-git-info) from 2.1.5 to 2.8.9.
    - [Release notes](https://github.com/npm/hosted-git-info/releases)
    - [Changelog](https://github.com/npm/hosted-git-info/blob/v2.8.9/CHANGELOG.md)
    - [Commits](https://github.com/npm/hosted-git-info/compare/v2.1.5...v2.8.9)
2021-05-11 Bump hosted-git-info in /Building Guide/assets/plugins/lightbox
    Bumps [hosted-git-info](https://github.com/npm/hosted-git-info) from 2.1.5 to 2.8.9.
    - [Release notes](https://github.com/npm/hosted-git-info/releases)
    - [Changelog](https://github.com/npm/hosted-git-info/blob/v2.8.9/CHANGELOG.md)
    - [Commits](https://github.com/npm/hosted-git-info/compare/v2.1.5...v2.8.9)
2021-08-04 Bump tar from 4.4.2 to 4.4.15 in /Building Guide/assets/plugins/lightbox
    Bumps [tar](https://github.com/npm/node-tar) from 4.4.2 to 4.4.15.
    - [Release notes](https://github.com/npm/node-tar/releases)
    - [Changelog](https://github.com/npm/node-tar/blob/main/CHANGELOG.md)
    - [Commits](https://github.com/npm/node-tar/compare/v4.4.2...v4.4.15)
    ---
    updated-dependencies:
2021-08-12 Bump path-parse in /Building Guide/assets/plugins/lightbox
    Bumps [path-parse](https://github.com/jbgutierrez/path-parse) from 1.0.5 to 1.0.7.
    - [Release notes](https://github.com/jbgutierrez/path-parse/releases)
    - [Commits](https://github.com/jbgutierrez/path-parse/commits/v1.0.7)
    ---
    updated-dependencies:
    - dependency-name: path-parse
2021-09-02 Bump tar from 4.4.2 to 4.4.19 in /Building Guide/assets/plugins/lightbox
    Bumps [tar](https://github.com/npm/node-tar) from 4.4.2 to 4.4.19.
    - [Release notes](https://github.com/npm/node-tar/releases)
    - [Changelog](https://github.com/npm/node-tar/blob/main/CHANGELOG.md)
    - [Commits](https://github.com/npm/node-tar/compare/v4.4.2...v4.4.19)
    ---
    updated-dependencies:
2022-02-11 Bump chownr in /Building Guide/assets/plugins/lightbox
    Bumps [chownr](https://github.com/isaacs/chownr) from 1.0.1 to 1.1.4.
    - [Release notes](https://github.com/isaacs/chownr/releases)
    - [Commits](https://github.com/isaacs/chownr/compare/v1.0.1...v1.1.4)
    ---
    updated-dependencies:
    - dependency-name: chownr
2022-04-27 Bump grunt in /Building Guide/assets/plugins/stickyfill
    Bumps [grunt](https://github.com/gruntjs/grunt) from 1.0.2 to 1.5.2.
    - [Release notes](https://github.com/gruntjs/grunt/releases)
    - [Changelog](https://github.com/gruntjs/grunt/blob/main/CHANGELOG)
    - [Commits](https://github.com/gruntjs/grunt/compare/v1.0.2...v1.5.2)
    ---
    updated-dependencies:
2022-05-25 Bump grunt in /Building Guide/assets/plugins/stickyfill
    Bumps [grunt](https://github.com/gruntjs/grunt) from 1.0.2 to 1.5.3.
    - [Release notes](https://github.com/gruntjs/grunt/releases)
    - [Changelog](https://github.com/gruntjs/grunt/blob/main/CHANGELOG)
    - [Commits](https://github.com/gruntjs/grunt/compare/v1.0.2...v1.5.3)
    ---
    updated-dependencies:
2022-11-10 Bump loader-utils in /Building Guide/assets/plugins/lightbox
    Bumps [loader-utils](https://github.com/webpack/loader-utils) from 1.1.0 to 1.4.1.
    - [Release notes](https://github.com/webpack/loader-utils/releases)
    - [Changelog](https://github.com/webpack/loader-utils/blob/v1.4.1/CHANGELOG.md)
    - [Commits](https://github.com/webpack/loader-utils/compare/v1.1.0...v1.4.1)
    ---
    updated-dependencies:
2022-11-17 Bump loader-utils in /Building Guide/assets/plugins/lightbox
    Bumps [loader-utils](https://github.com/webpack/loader-utils) from 1.1.0 to 1.4.2.
    - [Release notes](https://github.com/webpack/loader-utils/releases)
    - [Changelog](https://github.com/webpack/loader-utils/blob/v1.4.2/CHANGELOG.md)
    - [Commits](https://github.com/webpack/loader-utils/compare/v1.1.0...v1.4.2)
    ---
    updated-dependencies:
2022-12-05 Bump decode-uri-component in /Building Guide/assets/plugins/lightbox
    Bumps [decode-uri-component](https://github.com/SamVerschueren/decode-uri-component) from 0.2.0 to 0.2.2.
    - [Release notes](https://github.com/SamVerschueren/decode-uri-component/releases)
    - [Commits](https://github.com/SamVerschueren/decode-uri-component/compare/v0.2.0...v0.2.2)
    ---
    updated-dependencies:
    - dependency-name: decode-uri-component
2022-12-06 Bump qs in /Building Guide/assets/plugins/stickyfill
    Bumps [qs](https://github.com/ljharb/qs) from 6.5.2 to 6.11.0.
    - [Release notes](https://github.com/ljharb/qs/releases)
    - [Changelog](https://github.com/ljharb/qs/blob/main/CHANGELOG.md)
    - [Commits](https://github.com/ljharb/qs/compare/v6.5.2...v6.11.0)
    ---
    updated-dependencies:
2022-12-07 Bump qs from 6.5.1 to 6.5.3 in /Building Guide/assets/plugins/lightbox
    Bumps [qs](https://github.com/ljharb/qs) from 6.5.1 to 6.5.3.
    - [Release notes](https://github.com/ljharb/qs/releases)
    - [Changelog](https://github.com/ljharb/qs/blob/main/CHANGELOG.md)
    - [Commits](https://github.com/ljharb/qs/compare/v6.5.1...v6.5.3)
    ---
    updated-dependencies:
2022-12-31 Bump json5 and grunt-babel in /Building Guide/assets/plugins/stickyfill
    Bumps [json5](https://github.com/json5/json5) to 2.2.2 and updates ancestor dependency [grunt-babel](https://github.com/babel/grunt-babel). These dependencies need to be updated together.
    Updates `json5` from 0.5.1 to 2.2.2
    - [Release notes](https://github.com/json5/json5/releases)
    - [Changelog](https://github.com/json5/json5/blob/main/CHANGELOG.md)
    - [Commits](https://github.com/json5/json5/compare/v0.5.1...v2.2.2)
    Updates `grunt-babel` from 6.0.0 to 8.0.0
2023-01-06 Bump json5 and grunt-babel in /Building Guide/assets/plugins/stickyfill
    Bumps [json5](https://github.com/json5/json5) to 2.2.3 and updates ancestor dependency [grunt-babel](https://github.com/babel/grunt-babel). These dependencies need to be updated together.
    Updates `json5` from 0.5.1 to 2.2.3
    - [Release notes](https://github.com/json5/json5/releases)
    - [Changelog](https://github.com/json5/json5/blob/main/CHANGELOG.md)
    - [Commits](https://github.com/json5/json5/compare/v0.5.1...v2.2.3)
    Updates `grunt-babel` from 6.0.0 to 8.0.0
2023-01-12 Bump debug in /Building Guide/assets/plugins/lightbox
    Bumps [debug](https://github.com/debug-js/debug) from 2.6.0 to 2.6.9.
    - [Release notes](https://github.com/debug-js/debug/releases)
    - [Changelog](https://github.com/debug-js/debug/blob/2.6.9/CHANGELOG.md)
    - [Commits](https://github.com/debug-js/debug/compare/2.6.0...2.6.9)
    ---
    updated-dependencies:
